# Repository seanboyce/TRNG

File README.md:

# Function

This circuit is designed to output random bytes out MQTT, each as a message. It works at 8-10k bytes per second depending on system voltage and the fact that the bitrate of the entropy source is variable by nature.

# What? Why? You could just use a seed phrase and standard cryptography

Yeah, that works fine and there's no real disadvantage.

I've been designing various quantum TRNGs for nearly 15 years as part of an elaborate practical joke. This is just the latest one. I won't tell you what the joke is. Perhaps I'll never tell anyone. 

The world could do with a little more whimsy and playful mystery right now, and this is just my little bit that I can share with you.

# How it works

The core entropy source is two transistors in an unusual configuration. This is an old technique analogous to the classic "zener diode" method. It has the advantage of producing a slower signal, easier to sample.
It outputs avalanche noise with heavy DC bias. There's some nice [summary here](http://www.reallyreallyrandom.com/zener/why-its-random/index.html).

We remove the DC component wth a capacitor, then use two hex inverters for amplification and pulse-shaping. The first hex inverter is running at ~12V and is configured as two inverting amplifiers -- this is really power inefficient and it gets a bit warm due to the digital part working in linear modes. A little heat sink is recommended. 

This unusual use of the hex inverter is to reduce the parts count and cost -- I have a lot of hex inverters lying around. If you needed better power efficiency (e.g. for battery-powered use), you could use an op-amp. OPA132 is pretty easy to use.

The next hex inverter operates more or less digitally, just shaping the signal into a clean square wave. This one does not get warm.

After that, an Attiny261A acts as a Von Neumann extractor to convert the square wave into usable, unbiased bits of entropy. 

The bytes are read by a Pi Pico W and pushed out MQTT. Basic authentication works. I didn't bother adding TLS.

It would be possible to just use the PIO of the Pi Pico instead of an Attiny261A. However, most of the time I don't actually want the Pi Pico or Wi-Fi, and am just using the entropy locally. If you wanted to do this, you would simply not populate the Attiny261A, and solder a wire between pin 9 of the Attiny socket, and whatever pin you want on the Pi Pico. That will bypass the Attiny261A and push the raw entropy signal directly to the Pi Pico. I would recommend writing your own Von Neumann extractor with the PIO.

# How to build it

## Notes on surface mount components

This design makes extensive use of surface-mount components. I have limited budget and time to spend on my hobbies, so I generally use the smallest possible SMT components to save both (standardize my parts library). If you find 0402 difficult to work with, then it's very fast to open up the KiCAD files in this repo, and replace all the 0402 resistors with 0603 in the schematic. Then just pull up the board design, update from the schematic, and touch up the routing -- you should be good to go, 0603 is pretty easy to hand-solder even without a hot air rework station and solder paste. A normal iron, coil of solder, and some patience will suffice.

If you want to redesign everything as through-hole, this will require a bit of a redesign. I would recommend purchasing a USB boost converter, not populating the integrated boost converter, and using the passthrough I've left you (J2). Then switch the CD4069 to the DIP version, and add in through-hole resistors and capacitors. I vaguely recall that the DIP version of the CD4069 has better thermal dissipation, you might be able to get away with a smaller heat sink or none at all -- I've gotten away without one in older designs (give it a careful test though).

## Building the current design

I recommend building the boost converter first, then give it some power and make sure the output voltage is sane. Should be between 12 and 13 volts. Note that the EN pin of the MT3608 should be connected to Vin -- else nothing will output at all. I just bridge the middle pin of J1 to Vin.

Once that's in, I put in the transistors (mind polarity!), the first hex inverter, and all the resistors and capacitors around them. Then I supply power again, for a short time, with a scope connected to the output of the first hex inverter. The scope is set to be AC coupled. I should see a pretty looking signal with a lot of noise. Then I cut power -- that first hex inverter can get sort of hot with no heat sink attached.

Then I get the buck converter / LM7803 in, as well as the final hex inverter. Then I test as above (scope can be AC or DC coupled), making sure the signal from the second hex inverter is a weird looking, but mostly clean square wave ranging from 0 to 3.3V.

If that's good, I flash the program (main.asm) to an Attiny261A (using AVR-ICE, STK500 or home-made programmer). For the first few boards, I put in a socket for the AVR, so I can pull it out and update the firmware. Then I quickly check again, specifically that the "new output" pin of the Attiny261A is pushing out 10 usec pusles, and that bits are coming out of the pins of PORTA.

At this point, I just load the program (main.py) into the Pi Pico, disconnect it from the USB cable, and plug it in. The onboard LED should light up if it's receiving power, and flicker slightly if it's pushing out MQTT. If it doesn't flicker, try turning it off and on again, sometimes it can fail to connect to Wi-Fi.

**DO NOT plug a USB cable into the Pi Pico while it is connected to this circuit** It is being powered by 3.3V. USB is 5V. Several components are likely to make sad electronic noises, fail violently, and lose their magic blue smoke.

As for what part goes where? It's all in the KiCAD schematic. I would recommend giving it a detailed look.

## The Von Neumann Extractor

This just measures two time intervals between 2 sets of 2 independent events (it could probably use 3 events instead of 4 to calculate 2 intervals, but whatever. It's much faster than fast enough now). If t1>t2, it records a 0. If t1<t2, it records a 1. If they are equal, it tries again.

I originally wrote this firmware *ages* ago. It was quite an experience to look at my ham-fisted assembly from 15 years ago. I redid it with many optimizations, which increased performance about 50x. Also it consumes less power. Use main.asm, not old_von_neumann.asm. Seriously, the latter is pretty awful.

I include both files, so that one day I may look back and consider *both attempts* primitive and silly. Got to keep that ego in check!

## Photo

Note the black "bodge wire" near the USB power input. This was necessary because of an error in the original design files. The version in this repository has been corrected, and you won't need to cut any traces / add weird wires and so on.

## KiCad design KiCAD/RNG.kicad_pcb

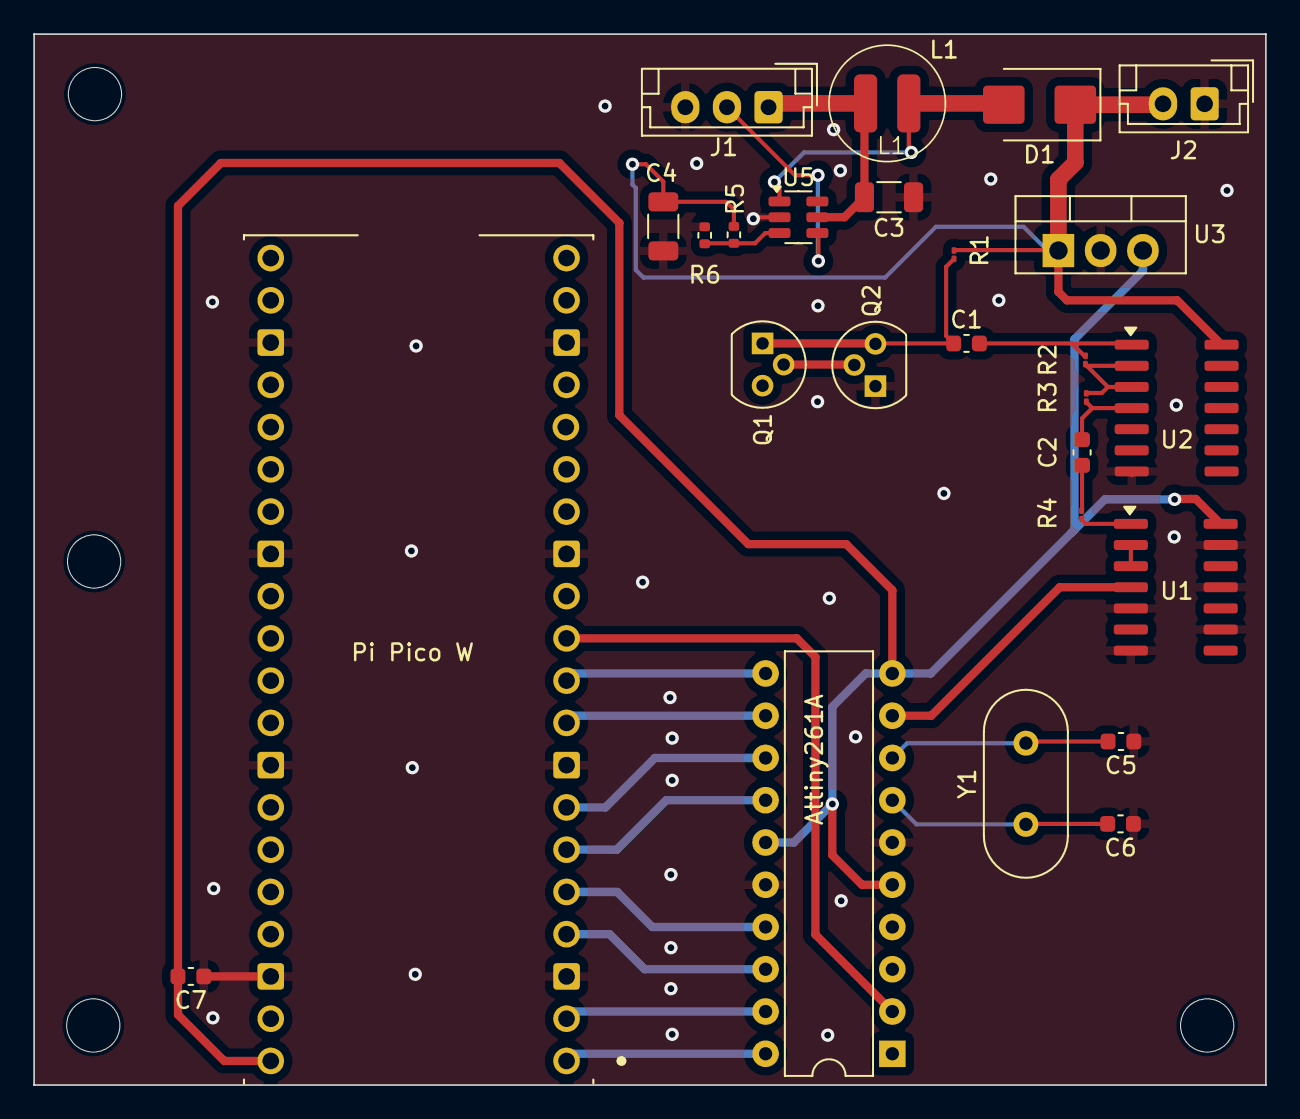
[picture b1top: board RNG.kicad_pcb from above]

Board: 2 copper layers, 74.0 x 63.2 mm, 28 parts (0 on the bottom side), 24 nets.

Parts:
A1: SC0918; MODULE_SC0918
C1, C2, C7: 0.1uF; C_0603_1608Metric
C3, C4: C; C_1206_3216Metric
C5, C6: 22pF; C_0603_1608Metric
D1: D_Schottky; D_SMB
H1, H2, H3, H4: MountingHole; MountingHole_3.2mm_M3
J1: Conn_01x03_Pin; JST_EH_B3B-EH-A_1x03_P2.50mm_Vertical
J2: Conn_01x02_Pin; JST_EH_B2B-EH-A_1x02_P2.50mm_Vertical
L1: L; cd32
Q1, Q2: 2N5551; TO-92
R1: 20k; R_01005_0402Metric
R2, R3: 100k; R_01005_0402Metric
R4: 1k; R_01005_0402Metric
R5, R6: R; R_0402_1005Metric
U3: LM7805_TO220; TO-220-3_Vertical
U5: MT3608; SOT-23-6
U6: ATtiny261A-P; DIP-20_W7.62mm
Y1: Crystal; Crystal_HC49-U_Vertical

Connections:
unnamed: A1.3 (GND), A1.8 (GND), A1.13 (GND), A1.18 (GND), A1.23 (GND), A1.28 (GND), A1.33 (AGND), A1.38 (GND), C3.1, C4.2, C5.1, C6.1, C7.1, J1.3, J2.1, Q1.1 (E), R6.2, U3.2 (GND), U5.2 (GND), U6.6 (GND), U6.16 (AGND)
unnamed: A1.1 (GP0), U6.20 (PA0)
unnamed: A1.2 (GP1), U6.19 (PA1)
unnamed: A1.4 (GP2), U6.18 (PA2)
unnamed: A1.5 (GP3), U6.17 (AREF/PA3)
unnamed: A1.6 (GP4), U6.14 (PA4)
unnamed: A1.7 (GP5), U6.13 (PA5)
unnamed: A1.9 (GP6), U6.12 (PA6)
unnamed: A1.10 (GP7), U6.11 (PA7)
unnamed: A1.11 (GP8), U6.2 (PB1)
unnamed: A1.40 (VBUS), C7.2, U3.3 (VO), U6.5 (VCC), U6.10 (~RESET/PB7), U6.15 (AVCC)
unnamed: C1.2, R2.1
unnamed: C2.1, R3.2
unnamed: C2.2, R4.1
unnamed: D1.2 (A), L1.2, U5.1 (SW)
unnamed: C4.1, D1.1 (K), J2.2, R1.1, R5.1, U3.1 (VI)
unnamed: C3.2, J1.1, L1.1, U5.5 (IN)
unnamed: J1.2, U5.4 (EN)
unnamed: Q1.2 (B), Q2.2 (B)
unnamed: C1.1, Q1.3 (C), Q2.1 (E), R1.2
unnamed: R2.2, R3.1
unnamed: R5.2, R6.1, U5.3 (FB)
unnamed: C6.2, U6.7 (XTAL1/PB4), Y1.1
unnamed: C5.2, U6.8 (XTAL2/PB5), Y1.2

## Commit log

2025-04-04 Update README.md
    Add initial notes
2025-04-05 Create BOM
2025-04-05 Rename BOM to BOM.md
2025-04-05 Update README.md
    Add assembly guide
2025-04-05 Update README.md
    wrong noise type
2025-04-05 Update README.md
    add link to supplemental info
2025-04-05 Update README.md
    add notes on ASM Von Neumann extractor.
2025-04-05 Create main.asm
    Add Von Neumann Extractor
2025-04-05 Update main.asm
    Bytes have 8 bits, not 7
2025-04-05 Update README.md
    update bitrate now that I remembered that bytes have more than 7 bits.
2025-04-05 Create main.py
    Add main micropython script for the Pi Pico
2025-04-05 Add files via upload
    Add scope trace images for reference
2025-04-06 Delete qtrng.jpg
    weird problems deleting file
2025-04-06 Update README.md
    Use newer, better photo
2025-04-06 Delete q_trng.jpg
    weird, why does the image suddenly look so dark? Fix exposure.
2025-04-06 Update README.md
    Add image with fixed exposure
2025-04-06 Update README.md
    Oh right, I should explain that bodge wire
2025-04-06 Update README.md
    Oh right, why did I build this thing?
2025-04-06 Update README.md
    Note on DIP CD4069 thermal dissipation.
2025-04-06 Update README.md
    Remove boring typographical errors, and introduce newer, better ones.
2025-04-07 Update BOM.md
    Forgot a coil in the BOM
2025-05-03 Add files via upload
    Add PDF of schematic so people without KiCAD installed can conveniently see it.
